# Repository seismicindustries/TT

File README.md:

# TT

alternative Hardware version of the Terminal Tedium from MXMXMX.

codec tested and ok
cv tested and ok

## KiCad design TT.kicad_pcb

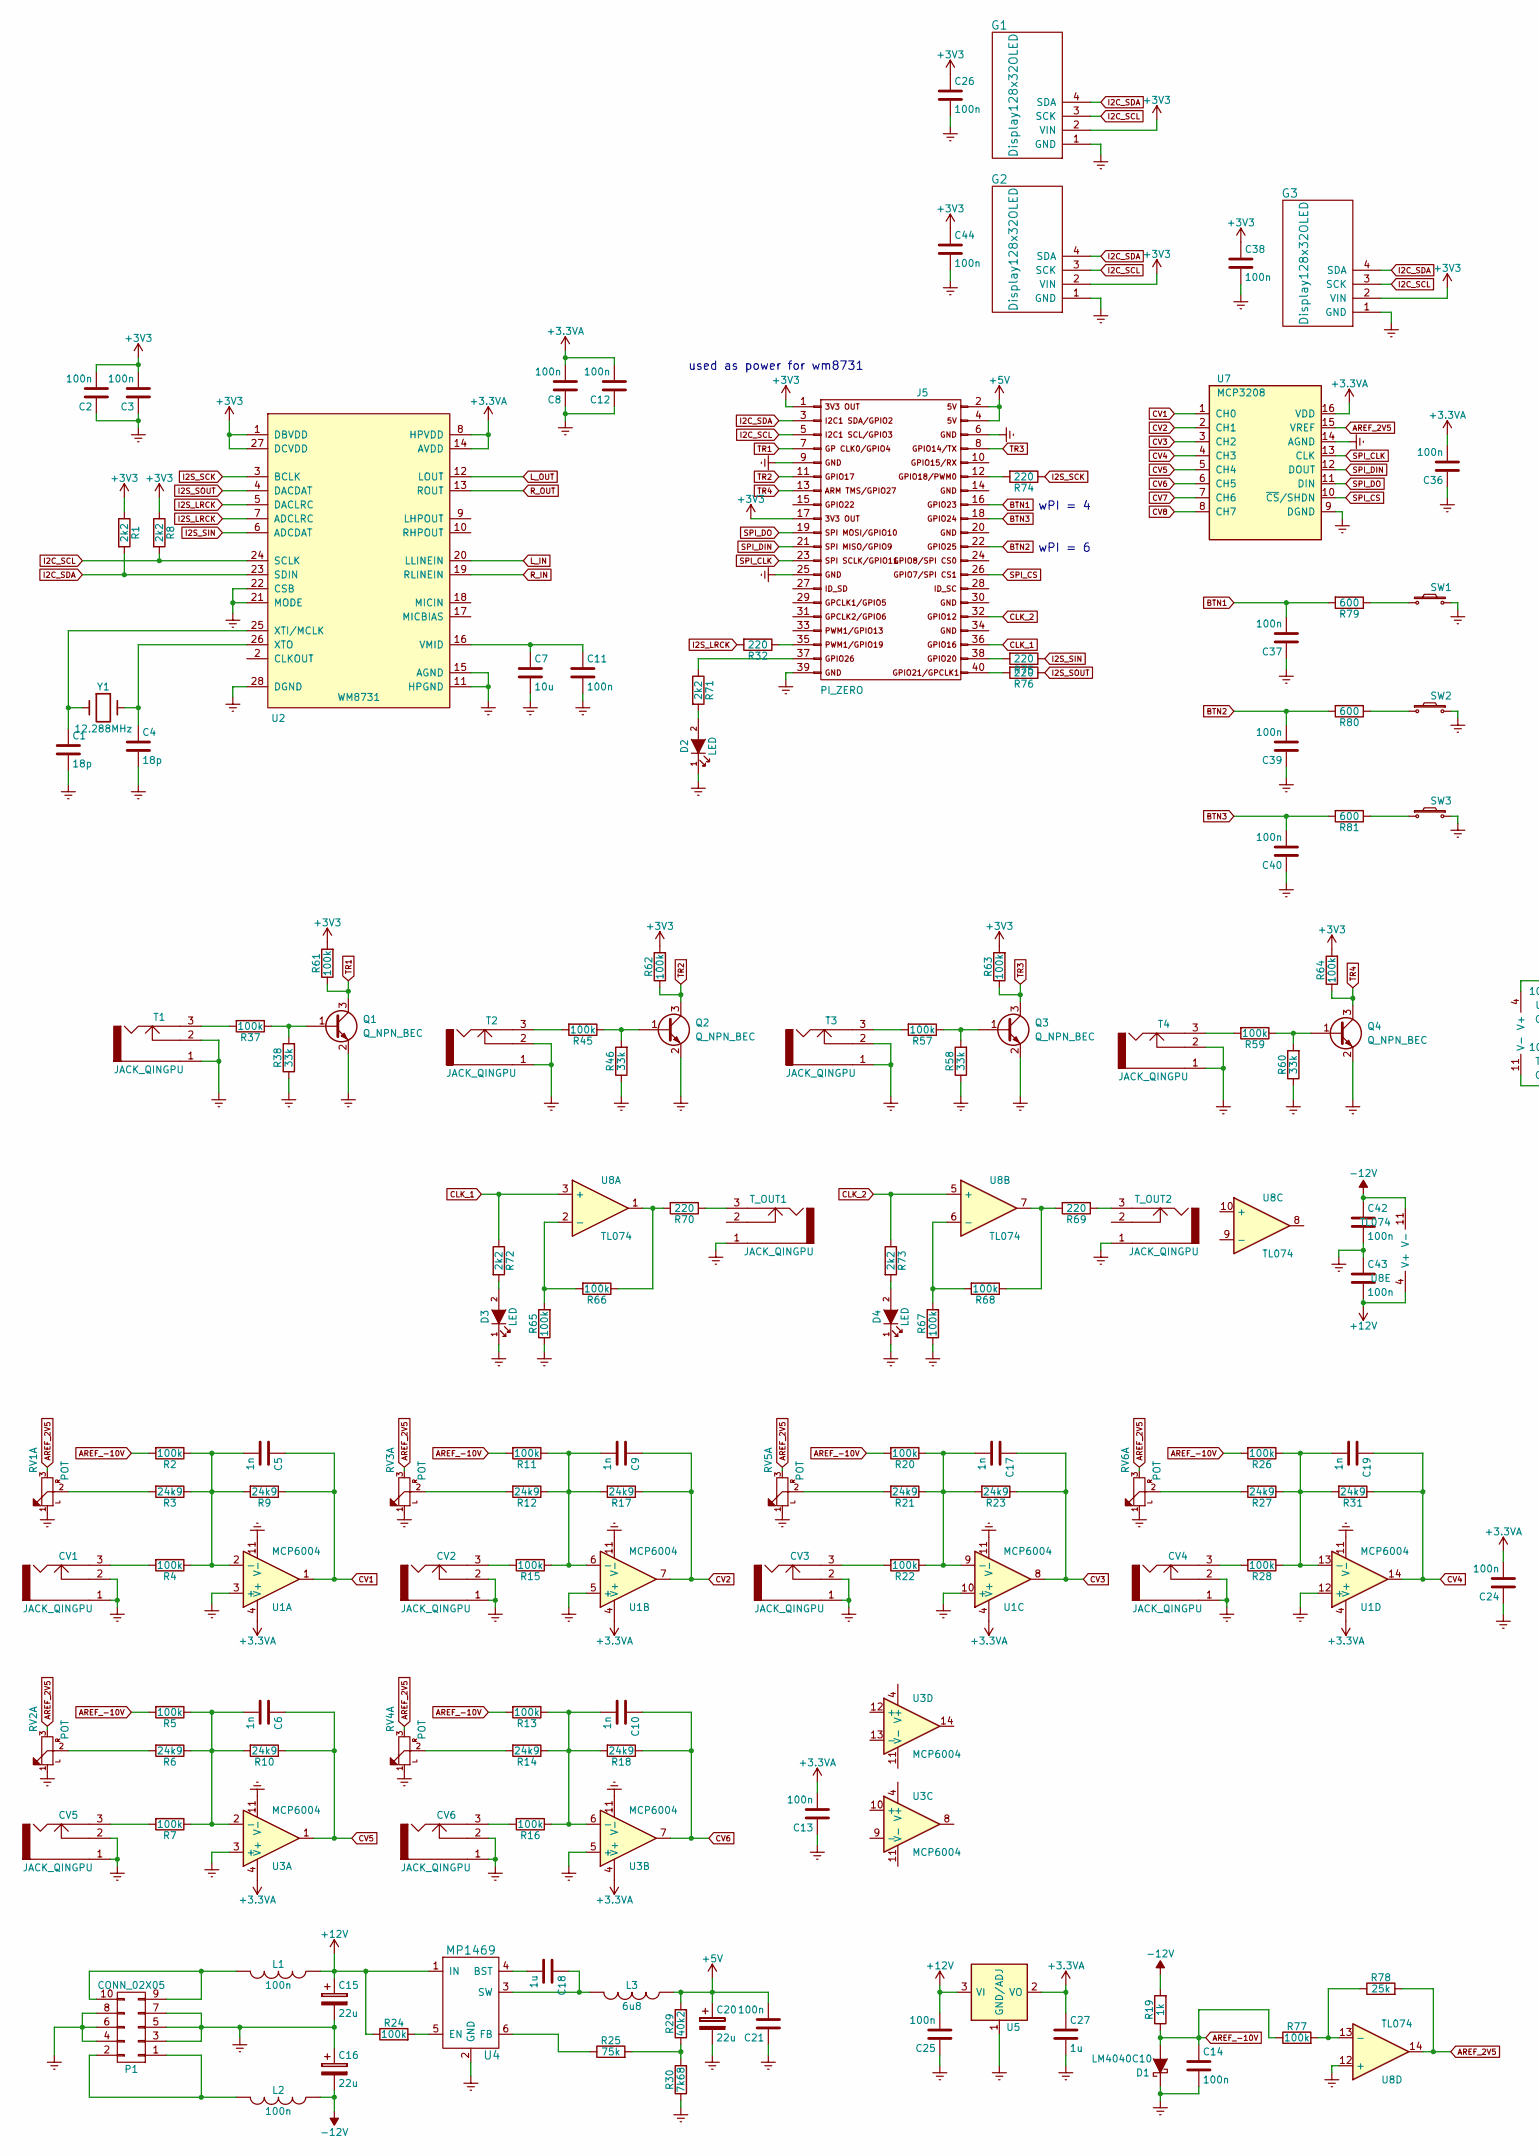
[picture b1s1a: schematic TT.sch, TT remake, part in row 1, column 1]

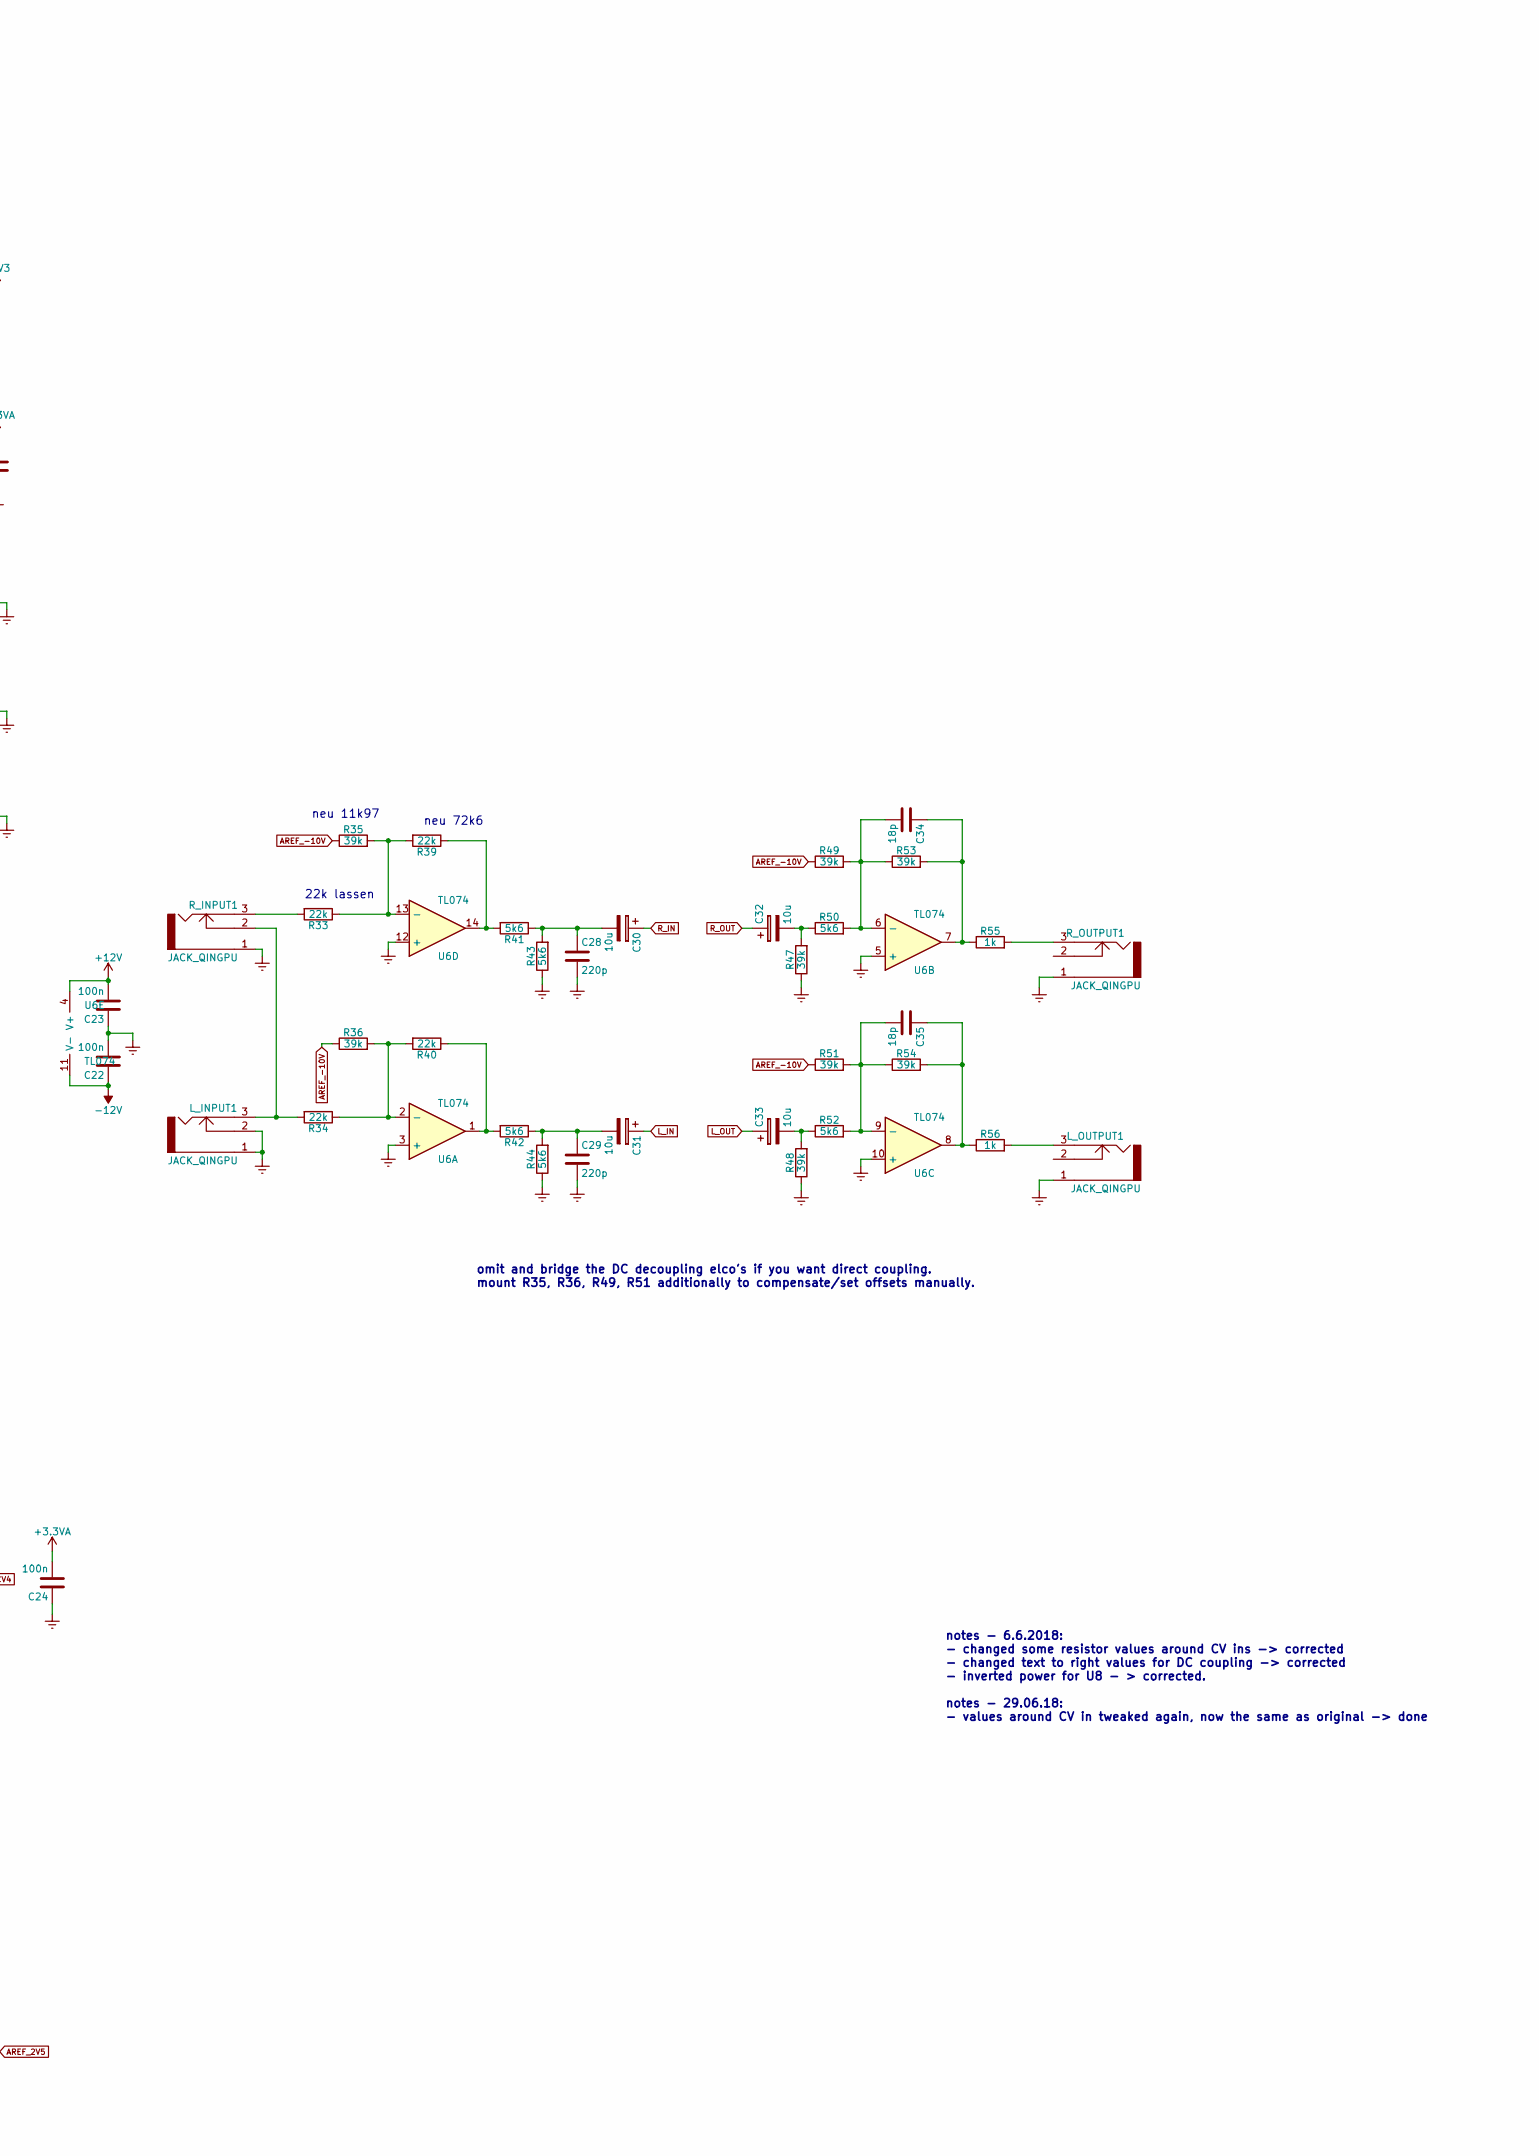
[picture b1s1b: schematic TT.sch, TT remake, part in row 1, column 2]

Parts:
C1, C4, C34, C35: 18p; C_0603; MPN VJ0603A180JXACW1BC
C2, C3, C8, C11, C12, C13, C14, C21, C22, C23, C24, C25, C26, C36, C37, C38, C39, C40, C42, C43, C44: 100n; C_0603; MPN 885012206095
C5, C6, C9, C10, C17, C19: 1n; C_0603; MPN GRM1885C1H102JA01D
C7: 10u; C_0603; Mouser Part Nr 810-C1608X5R0J106M
C15, C16, C20: 22u; CP_Elec_7.3x4.3; MPN EEF-CX1D220R
C18, C27: 1u; C_0603; MPN 885012206095
C28, C29: 220p; C_0603; MPN GRM1885C1H221JA01J
C30, C31, C32, C33: 10u; C_Radial_D4_L7; MPN UPW1E100MDD6
CV1, CV2, CV3, CV4, CV5, CV6: JACK_QINGPU; jack_qingpu
D1: LM4040C10; SOT-23; MPN LM4040C10IDBZR
D2, D3, D4: LED; LED_D3.0mm; MPN LTL-4231N
G1, G2, G3: Display128x32OLED; oled_128x32
J5: PI_ZERO
L1, L2: 100n; Inductor_PSU_NLCV32T; MPN NLCV32T-R10M-PFR
L3: 6u8; Inductor_SRN4018TA_bourns; MPN SRN4018TA-6R8M
L_INPUT1: JACK_QINGPU; jack_qingpu
L_OUTPUT1: JACK_QINGPU; jack_qingpu
P1: CONN_02X05; Pin_Header_Angled_2x05_Pitch2.54mm_with_space_for_con; MPN 649-68020-110HLF
Q1, Q2, Q3, Q4: Q_NPN_BEC; SOT-23; MPN BC847CLT1G
R1, R8, R71, R72, R73: 2k2; R_0603; MPN RC0603FR-072K2L
R2, R5, R11, R13, R20, R26: 100k; R_0603; MPN RC0603FR-07200KL
R3, R6, R12, R14, R21, R27: 24k9; R_0603; MPN RCA0603100KJNEC
R4, R7, R15, R16, R22, R24, R28, R37, R45, R57, R59, R61, R62, R63, R64, R65, R66, R67, R68, R77: 100k; R_0603; MPN RCA0603100KJNEC
R9, R10, R17, R18, R23, R31: 24k9; R_0603; MPN ERJ-3GEYJ333V
R19: 1k; R_0603; MPN ERJ-3GEYJ333V
R25: 75k; R_0603; MPN CR0603-FX-2202ELF
R29: 40k2; R_0603; MPN CR0603-FX-2202ELF
R30: 7k68; R_0603; MPN CR0603-FX-2202ELF
R32, R69, R70, R74, R75, R76: 220; R_0603; MPN RCA0603100KJNEC
R33, R34, R39, R40: 22k; R_0603; MPN CR0603-FX-2202ELF
R35, R36, R47, R48, R49, R51, R53, R54: 39k; R_0603; MPN ERJ-3GEYJ393V
R38, R46, R58, R60: 33k; R_0603; MPN ERJ-3GEYJ333V
R41, R42, R43, R44, R50, R52: 5k6; R_0603; MPN CR0603-FX-5601ELF
R55, R56: 1k; R_0603; MPN RC0603FR-071KL
R78: 25k; R_0603; MPN ERJ-3GEYJ333V
R79, R80, R81: 600; R_0603; MPN RCA0603100KJNEC
RV1, RV2, RV3, RV4, RV5, RV6: POT; Potentiometer_ALPHA_RV112
R_INPUT1: JACK_QINGPU; jack_qingpu
R_OUTPUT1: JACK_QINGPU; jack_qingpu
SW1, SW2, SW3: SW_PUSH_SMALL_H; APEM_tactile_SMD_switch_6mm; MPN ADTSM66NV
T1, T2, T3, T4: JACK_QINGPU; jack_qingpu
T_OUT1, T_OUT2: JACK_QINGPU; jack_qingpu
U1, U3: MCP6004; SOIC-14_N; MPN MCP6004T-I/SL SOIC-14 variant
U2: WM8731; SSOP-28_5.3x10.2mm_Pitch0.65mm; MPN WM8731SEDS/V
U4: MP1469; SOT-23-6; MPN MP1469GJ-Z
U5: SOT-223; MPN AZ1117IH-3.3TRG1 SOT-223-3 variant
U6, U8: TL074; SOIC-14_N; MPN 595-TL074CDR SOIC-14 variant
U7: MCP3208; SO-16-N
Y1: 12.288MHz; ABM7; Mouser Part Nr 815-ABM7-12.2-D2Y-T

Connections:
+3.3VA: C8.2, C12.2, C13.2, C24.2, C27.1, C36.2, U1.4 (V+), U2.8 (HPVDD), U2.14 (AVDD), U3.4 (V+), U5.2 (VO), U7.16 (VDD)
+3V3: C2.2, C3.2, C26.1, C38.1, C44.1, G1.2 (VIN), G2.2 (VIN), G3.2 (VIN), J5.1, J5.17, R1.1, R8.1, R61.2, R62.2, R63.2, R64.2, U2.1 (DBVDD), U2.27 (DCVDD)
+5V: C20.1, C21.2, J5.2, J5.4, L3.1, R29.2
+12V: C15.1, C23.2, C25.2, C43.2, L1.1, R24.1, U4.1 (IN), U5.3 (VI), U6.4 (V+), U8.4 (V+)
-12V: C16.2, C22.1, C42.1, L2.1, R19.2, U6.11 (V-), U8.11 (V-)
AREF_2V5: R78.2, RV1.3 (6), RV2.3 (6), RV3.3 (6), RV4.3 (6), RV5.3 (6), RV6.3 (6), U7.15 (VREF), U8.14
AREF_-10V: C14.1, D1.2 (A), R2.2, R5.2, R11.2, R13.2, R19.1, R20.2, R26.2, R35.1, R36.1, R49.1, R51.1, R77.1
BTN1: C37.2, J5.16, R79.2
BTN2: C39.2, J5.22, R80.2
BTN3: C40.2, J5.18, R81.2
CLK_1: J5.36, R72.1, U8.3 (+)
CLK_2: J5.32, R73.1, U8.5 (+)
CV1: C5.1, R9.1, U1.1, U7.1 (CH0)
CV2: C9.1, R17.1, U1.7, U7.2 (CH1)
CV3: C17.1, R23.1, U1.8, U7.3 (CH2)
CV4: C19.1, R31.1, U1.14, U7.4 (CH3)
CV5: C6.1, R10.1, U3.1, U7.5 (CH4)
CV6: C10.1, R18.1, U3.7, U7.6 (CH5)
Earth: C1.2, C2.1, C3.1, C4.2, C7.2, C8.1, C11.2, C12.1, C13.1, C14.2, C15.2, C16.1, C20.2, C21.1, C22.2, C23.1, C24.1, C25.1, C26.2, C27.2, C28.2, C29.2, C36.1, C37.1, C38.2, C39.1, C40.1, C42.2, C43.1, C44.2, CV1.1, CV1.2, CV2.1, CV2.2, CV3.1, CV3.2, CV4.1, CV4.2, CV5.1, CV5.2, CV6.1, CV6.2, D1.1 (K), D2.1 (K), D3.1 (K), D4.1 (K), G1.1 (GND), G2.1 (GND), G3.1 (GND), J5.6, J5.9, J5.25, J5.39, L_INPUT1.1, L_INPUT1.2, L_OUTPUT1.1, P1.3, P1.4, P1.5, P1.6, P1.7, P1.8, Q1.2 (E), Q2.2 (E), Q3.2 (E), Q4.2 (E), R30.1, R38.1, R43.1, R44.1, R46.1, R47.1, R48.1, R58.1, R60.1, R65.1, R67.1, RV1.1 (4), RV2.1 (4), RV3.1 (4), RV4.1 (4), RV5.1 (4), RV6.1 (4), R_INPUT1.1, R_OUTPUT1.1, SW1.2, SW2.2, SW3.2, T1.1, T1.2, T2.1, T2.2, T3.1, T3.2, T4.1, T4.2, T_OUT1.1, T_OUT2.1, U1.3 (+), U1.5 (+), U1.10 (+), U1.11 (V-), U1.12 (+), U2.11 (HPGND), U2.15 (AGND), U2.21 (MODE), U2.22 (CSB), U2.28 (DGND), U3.3 (+), U3.5 (+), U3.11 (V-), U4.2 (GND), U5.1 (GND/ADJ), U6.3 (+), U6.5 (+), U6.10 (+), U6.12 (+), U7.9 (DGND), U7.14 (AGND), U8.12 (+)
I2C_SCL: G1.3 (SCK), G2.3 (SCK), G3.3 (SCK), J5.5, R8.2, U2.24 (SCLK)
I2C_SDA: G1.4 (SDA), G2.4 (SDA), G3.4 (SDA), J5.3, R1.2, U2.23 (SDIN)
I2S_LRCK: R32.2, U2.5 (DACLRC), U2.7 (ADCLRC)
I2S_SCK: R74.1, U2.3 (BCLK)
I2S_SIN: R75.1, U2.6 (ADCDAT)
I2S_SOUT: R76.1, U2.4 (DACDAT)
L_IN: C31.1, U2.20 (LLINEIN)
L_OUT: C33.1, U2.12 (LOUT)
unnamed: C1.1, U2.25 (XTI/MCLK), Y1.1
unnamed: C4.1, U2.26 (XTO), Y1.2
unnamed: C5.2, R2.1, R3.1, R4.1, R9.2, U1.2 (-)
unnamed: C6.2, R5.1, R6.1, R7.1, R10.2, U3.2 (-)
unnamed: C9.2, R11.1, R12.1, R15.1, R17.2, U1.6 (-)
unnamed: C10.2, R13.1, R14.1, R16.1, R18.2, U3.6 (-)
unnamed: C7.1, C11.1, U2.16 (VMID)
unnamed: C17.2, R20.1, R21.1, R22.1, R23.2, U1.9 (-)
unnamed: C18.1, L3.2, U4.3 (SW)
unnamed: C18.2, U4.4 (BST)
unnamed: C19.2, R26.1, R27.1, R28.1, R31.2, U1.13 (-)
unnamed: C28.1, C30.2, R41.1, R43.2
unnamed: C29.1, C31.2, R42.1, R44.2
unnamed: C32.2, R47.2, R50.1
unnamed: C33.2, R48.2, R52.1
unnamed: C34.1, R53.2, R55.1, U6.7
unnamed: C34.2, R49.2, R50.2, R53.1, U6.6 (-)
unnamed: C35.1, R54.2, R56.1, U6.8
unnamed: C35.2, R51.2, R52.2, R54.1, U6.9 (-)
unnamed: CV1.3, R4.2
unnamed: CV2.3, R15.2
unnamed: CV3.3, R22.2
unnamed: CV4.3, R28.2
unnamed: CV5.3, R7.2
unnamed: CV6.3, R16.2
unnamed: D2.2 (A), R71.2
unnamed: D3.2 (A), R72.2
unnamed: D4.2 (A), R73.2
unnamed: J5.12, R74.2
unnamed: J5.35, R32.1
unnamed: J5.37, R71.1
unnamed: J5.38, R75.2
unnamed: J5.40, R76.2
unnamed: L1.2, P1.9, P1.10
unnamed: L2.2, P1.1, P1.2
unnamed: L_INPUT1.3, R34.2, R_INPUT1.2
unnamed: L_OUTPUT1.3, R56.2
unnamed: Q1.1 (B), R37.1, R38.2
unnamed: Q2.1 (B), R45.1, R46.2
unnamed: Q3.1 (B), R57.1, R58.2
unnamed: Q4.1 (B), R59.1, R60.2
unnamed: R3.2, RV1.2 (5)
unnamed: R6.2, RV2.2 (5)
unnamed: R12.2, RV3.2 (5)
unnamed: R14.2, RV4.2 (5)
unnamed: R21.2, RV5.2 (5)
unnamed: R24.2, U4.5 (EN)
unnamed: R25.1, U4.6 (FB)
unnamed: R25.2, R29.1, R30.2
unnamed: R27.2, RV6.2 (5)
unnamed: R33.1, R35.2, R39.2, U6.13 (-)
unnamed: R33.2, R_INPUT1.3
unnamed: R34.1, R36.2, R40.2, U6.2 (-)
unnamed: R37.2, T1.3
unnamed: R39.1, R41.2, U6.14
unnamed: R40.1, R42.2, U6.1
unnamed: R45.2, T2.3
unnamed: R55.2, R_OUTPUT1.3
unnamed: R57.2, T3.3
unnamed: R59.2, T4.3
unnamed: R65.2, R66.2, U8.2 (-)
unnamed: R66.1, R70.2, U8.1
unnamed: R67.2, R68.2, U8.6 (-)
unnamed: R68.1, R69.2, U8.7
unnamed: R69.1, T_OUT2.3
unnamed: R70.1, T_OUT1.3
unnamed: R77.2, R78.1, U8.13 (-)
unnamed: R79.1, SW1.1
unnamed: R80.1, SW2.1
unnamed: R81.1, SW3.1
R_IN: C30.1, U2.19 (RLINEIN)
R_OUT: C32.1, U2.13 (ROUT)
SPI_CLK: J5.23, U7.13 (CLK)
SPI_CS: J5.26, U7.10 (~CS~/SHDN)
SPI_DIN: J5.21, U7.12 (DOUT)
SPI_DO: J5.19, U7.11 (DIN)
TR1: J5.7, Q1.3 (C), R61.1
TR2: J5.11, Q2.3 (C), R62.1
TR3: J5.8, Q3.3 (C), R63.1
TR4: J5.13, Q4.3 (C), R64.1

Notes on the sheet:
omit and bridge the DC decoupling elco's if you want direct coupling. mount R35, R36, R49, R51 additionally to compensate/set offsets manually.
neu 72k6
22k lassen
neu 11k97
used as power for wm8731
wPI = 4
wPI = 6
notes - 6.6.2018: - changed some resistor values around CV ins -> corrected - changed text to right values for DC coupling -> corrected - inverted power for U8 - > corrected. notes - 29.06.18: - values around CV in tweaked again, now the same as original -> done

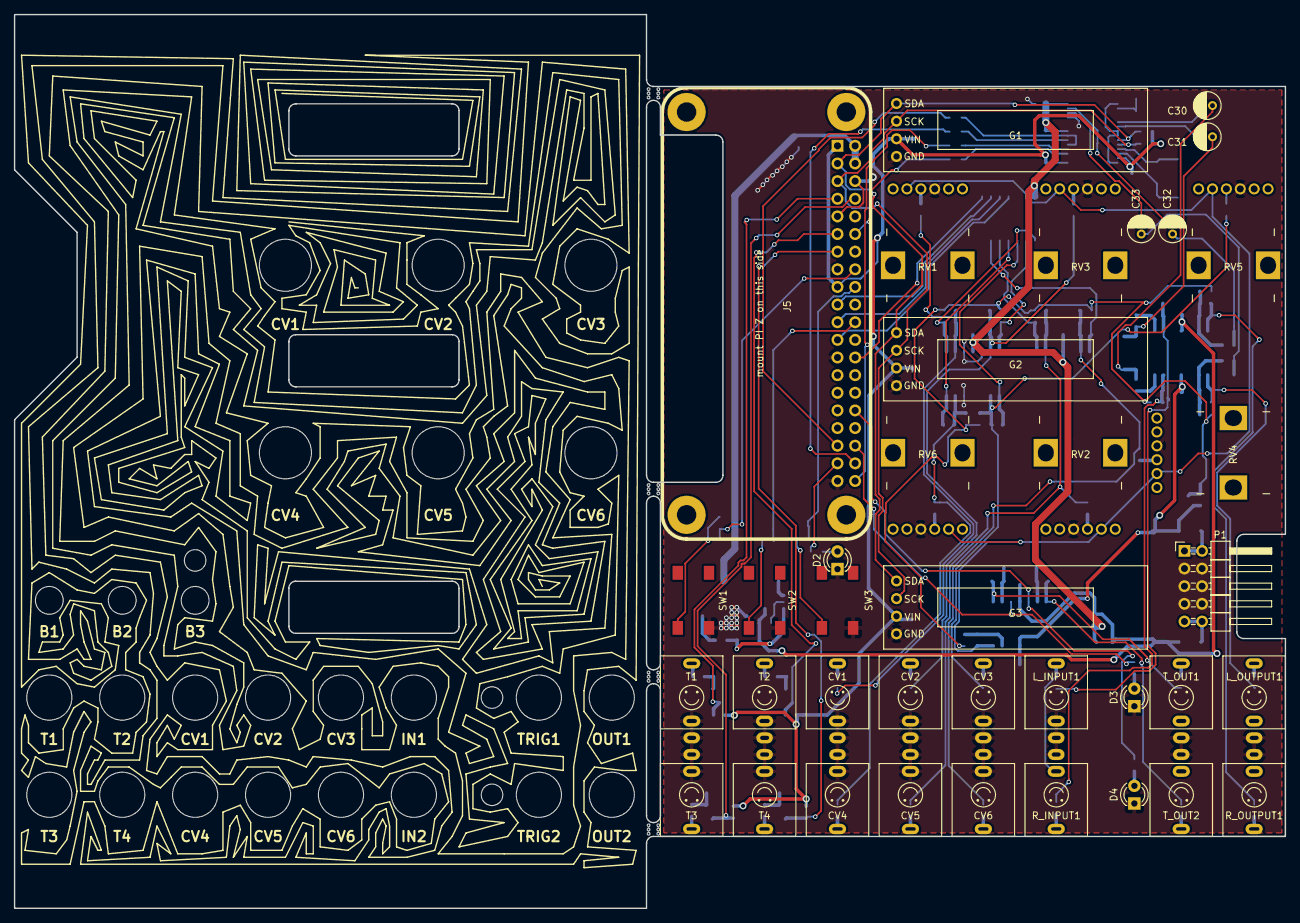
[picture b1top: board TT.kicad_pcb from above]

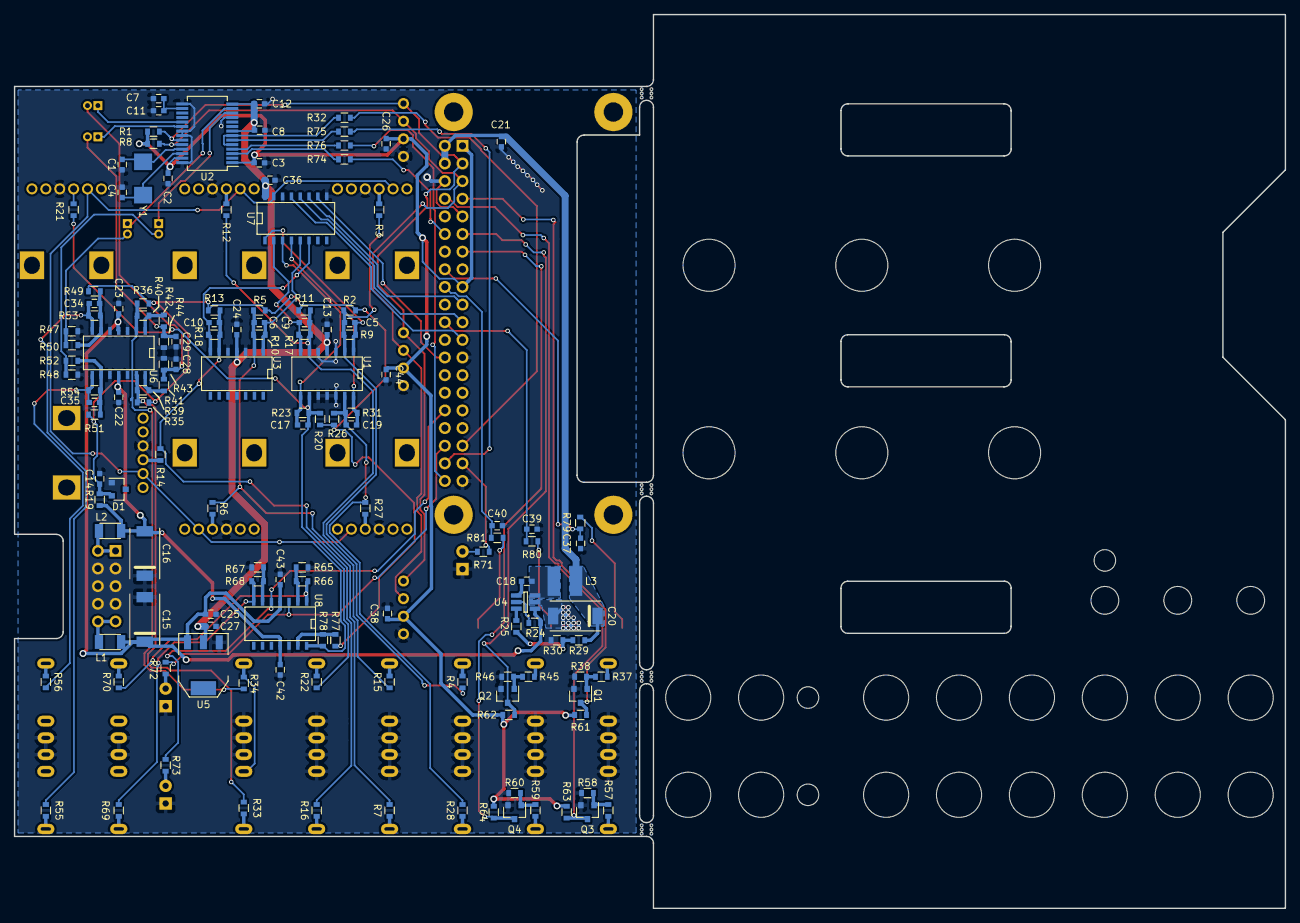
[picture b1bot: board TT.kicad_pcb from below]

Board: 2 copper layers, 183.0 x 128.7 mm, 174 parts (137 on the bottom side), 107 nets.

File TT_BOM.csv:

Refs,Value,Footprint,QTY,MFR,MPN,SPR,SPN
Y1,12.288MHz,raffilibkicad:ABM7,1,ABRACON,ABM7-12.288MHZ-D2Y-T,Mouser,815-ABM7-12.2-D2Y-T
SW1;SW2;SW3,SW_PUSH_SMALL_H,raffilibkicad:APEM_tactile_SMD_switch_6mm,3,APEM,ADTSM66NV,Mouser,642-ADTSM66NV
C15;C16;C20,22u,raffilibkicad:CP_Elec_7.3x4.3,3,Panasonic,EEF-CX1D220R,Mouser,667-EEF-CX1D220R
C22;C23;C14;C24;C3;C2;C12;C8;C11;C25;C26;C21;C13;C42;C43;C44;C38;C36;C39;C37;C40,100n,raffilibkicad:C_0603,21,Wurth Electronics,885012206095,Mouser,710-885012206095
C7,10u,raffilibkicad:C_0603,1,TDK,C1608X5R0J106M080AB,Mouser,810-C1608X5R0J106M
C1;C4;C34;C35,18p,raffilibkicad:C_0603,4,Vishay / Vitramon,VJ0603A180JXACW1BC,Mouser,77-VJ0603A180JXACBC
C5;C9;C17;C19;C6;C10,1n,raffilibkicad:C_0603,6,Murata Electronics,GRM1885C1H102JA01D,Mouser,81-GRM39C102J50
C27;C18,1u,raffilibkicad:C_0603,2,Wurth Electronics,885012206095,Mouser,710-885012206095
C28;C29,220p,raffilibkicad:C_0603,2,Murata Electronics,GRM1885C1H221JA01J,Mouser,81-GRM1885C1H221JA
C30;C31;C32;C33,10u,raffilibkicad:C_Radial_D4_L7,4,Nichicon,UPW1E100MDD6,Mouser,647-UPW1E100MDD6
L1;L2,100n,raffilibkicad:Inductor_PSU_NLCV32T,2,TDK,NLCV32T-R10M-PFR,Mouser,810-NLCV32T-R10M-PFR
L3,6u8,raffilibkicad:Inductor_SRN4018TA_bourns,1,Bourns,SRN4018TA-6R8M,Mouser,652-SRN4018TA-6R8M
D2;D3;D4,LED,raffilibkicad:LED_D3.0mm,3,Lite-On,LTL-4231N,Mouser,859-LTL-4231N
J5,PI_ZERO,raffilibkicad:PI_ZERO,1,,,,
P1,CONN_02X05,raffilibkicad:Pin_Header_Angled_2x05_Pitch2.54mm_with_space_for_con,1,Amphenol FCI,649-68020-110HLF,Mouser,68020-110HLF
RV1;RV3;RV5;RV6;RV2;RV4,POT,raffilibkicad:Potentiometer_ALPHA_RV112,6,,,,
R4;R15;R24;R22;R28;R37;R45;R57;R59;R3;R12;R21;R27;R7;R16;R6;R14;R63;R64;R62;R61;R66;R65;R68;R67;R77,100k,raffilibkicad:R_0603,26,Vishay / Draloric,RCA0603100KJNEC,Mouser,71-RCA0603100KJNEC
R55;R56;R19,1k,raffilibkicad:R_0603,3,Yageo,RC0603FR-071KL,Mouser,603-RC0603FR-071KL
R2;R11;R20;R26;R5;R13,200k,raffilibkicad:R_0603,6,Yageo,RC0603FR-07200KL,Mouser,603-RC0603FR-07200KL
R69;R70;R32;R74;R75;R76,220,raffilibkicad:R_0603,6,Vishay / Draloric,RCA0603100KJNEC,Mouser,71-RCA0603100KJNEC
R33;R34;R40;R39,22k,raffilibkicad:R_0603,4,Bourns,CR0603-FX-2202ELF,Mouser,652-CR0603FX-2202ELF
R78,25k,raffilibkicad:R_0603,1,Panasonic,ERJ-3GEYJ333V,Mouser,667-ERJ-3GEYJ333V
R8;R1;R71;R72;R73,2k2,raffilibkicad:R_0603,5,Yageo,RC0603FR-072K2L,Mouser,603-RC0603FR-072K2L
R9;R17;R23;R31;R38;R46;R58;R60;R10;R18,33k,raffilibkicad:R_0603,10,Panasonic,ERJ-3GEYJ333V,Mouser,667-ERJ-3GEYJ333V
R47;R53;R48;R54;R49;R51;R36;R35,39k,raffilibkicad:R_0603,8,Panasonic,ERJ-3GEYJ393V,Mouser,667-ERJ-3GEYJ393V
R29,40k2,raffilibkicad:R_0603,1,Bourns,CR0603-FX-2202ELF,Mouser,652-CR0603FX-2202ELF
R41;R42;R43;R44;R50;R52,5k6,raffilibkicad:R_0603,6,Bourns,CR0603-FX-5601ELF,Mouser,652-CR0603FX-5601ELF
R80;R79;R81,600,raffilibkicad:R_0603,3,Vishay / Draloric,RCA0603100KJNEC,Mouser,71-RCA0603100KJNEC
R25,75k,raffilibkicad:R_0603,1,Bourns,CR0603-FX-2202ELF,Mouser,652-CR0603FX-2202ELF
R30,7k68,raffilibkicad:R_0603,1,Bourns,CR0603-FX-2202ELF,Mouser,652-CR0603FX-2202ELF
U7,MCP3208,raffilibkicad:SO-16-N,1,,,Mouser,579-MCP3208CISL
U1;U3,MCP6004,raffilibkicad:SOIC-14_N,2,Microchip Technology,MCP6004T-I/SL SOIC-14 variant,Mouser,579-MCP6004T-I/SL
U6;U8,TL074,raffilibkicad:SOIC-14_N,2,Texas Instruments,595-TL074CDR SOIC-14 variant,Mouser,595-TL074CDR
D1,LM4040C10,raffilibkicad:SOT-23,1,Texas Instruments,LM4040C10IDBZR,Mouser,595-LM4040C10IDBZR
Q1;Q2;Q3;Q4,Q_NPN_BEC,raffilibkicad:SOT-23,4,ON Semiconductor,BC847CLT1G,Mouser,863-BC847CLT1G
U4,MP1469,raffilibkicad:SOT-23-6,1,MPS,MP1469GJ-Z,Mouser,946-MP1469GJZ
U2,WM8731,raffilibkicad:SSOP-28_5.3x10.2mm_Pitch0.65mm,1,Cirrus Logic,WM8731SEDS/V,Mouser,238-WM8731SEDS/V
L_INPUT1;R_INPUT1;L_OUTPUT1;R_OUTPUT1;CV1;CV2;CV3;CV4;T1;T2;T3;T4;CV5;CV6;T_OUT1;T_OUT2,JACK_QINGPU,raffilibkicad:jack_qingpu,16,Qingpu,,Qingpu,
G1;G2;G3,Display128x32OLED,raffilibkicad:oled_128x32,3,,,,

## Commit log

2018-05-30 first upload
2018-05-30 added readme
2018-05-30 .sch cleanup
2018-06-06 corrected some values and the power inversion of U8
2018-06-29 CV input stage values tweaked to original
